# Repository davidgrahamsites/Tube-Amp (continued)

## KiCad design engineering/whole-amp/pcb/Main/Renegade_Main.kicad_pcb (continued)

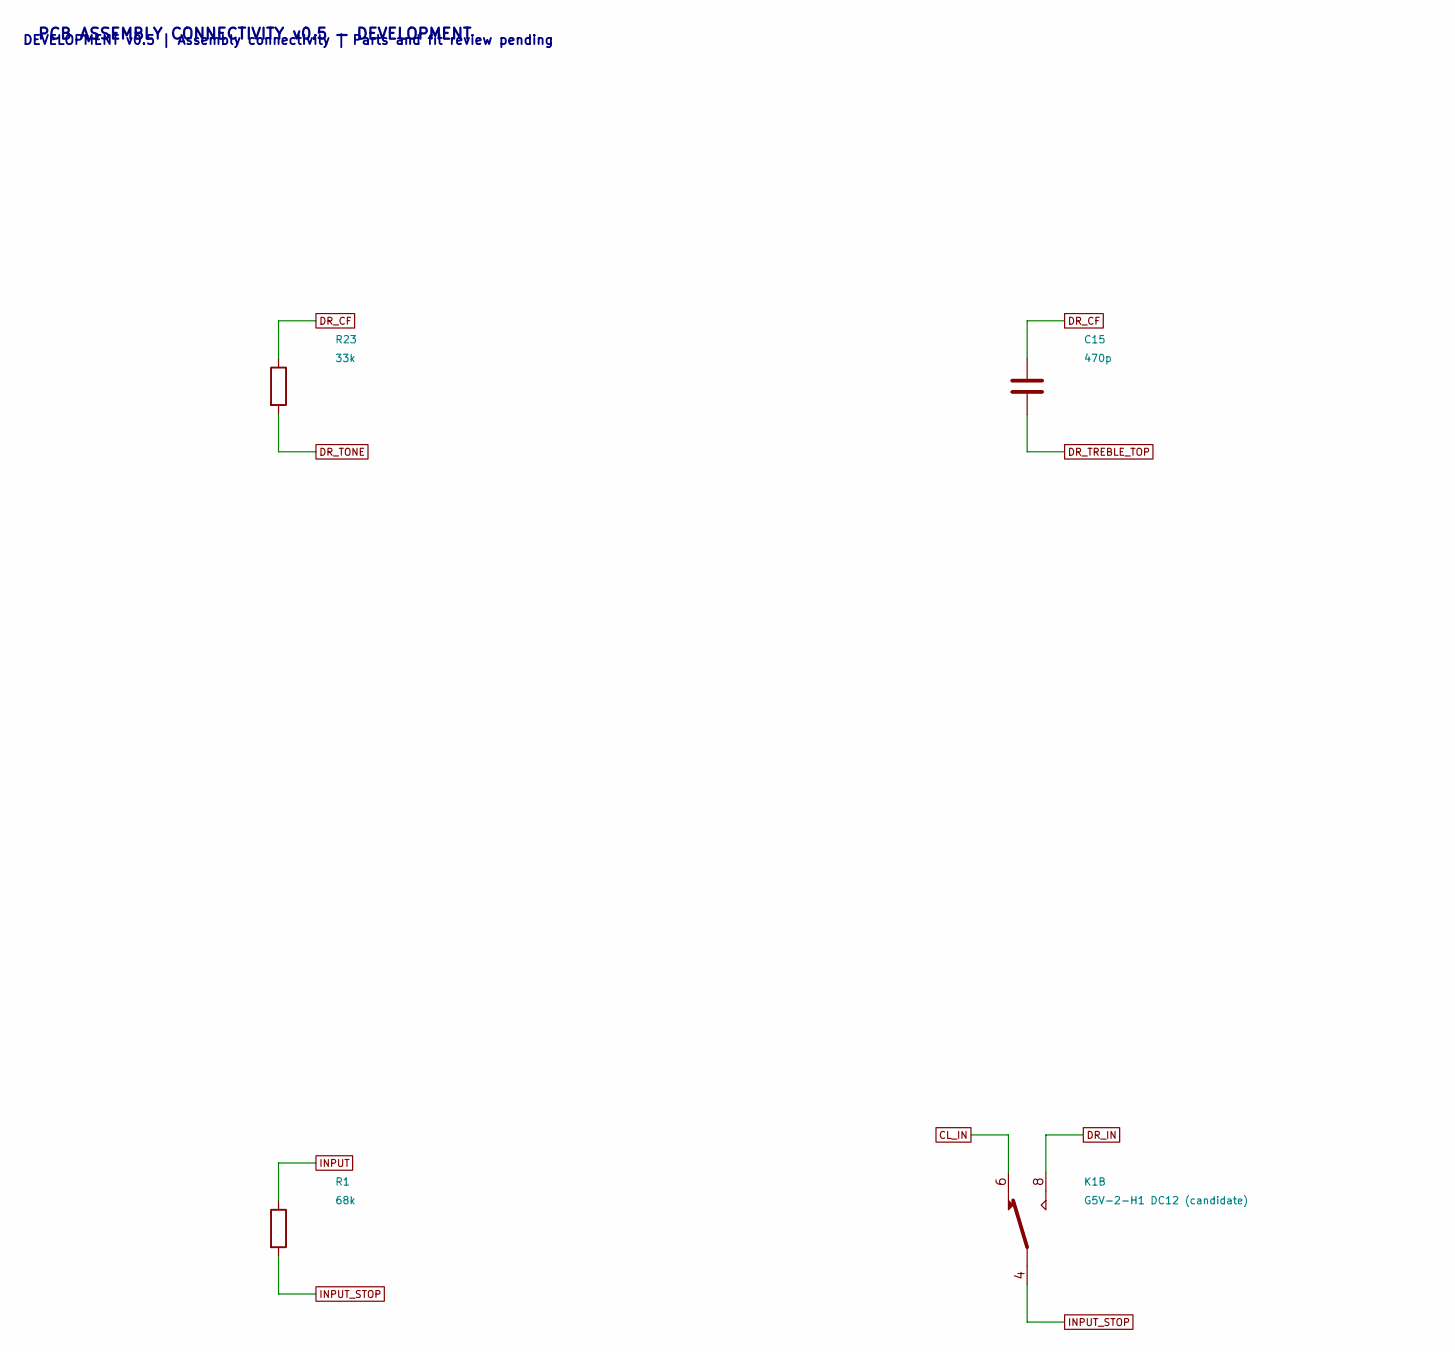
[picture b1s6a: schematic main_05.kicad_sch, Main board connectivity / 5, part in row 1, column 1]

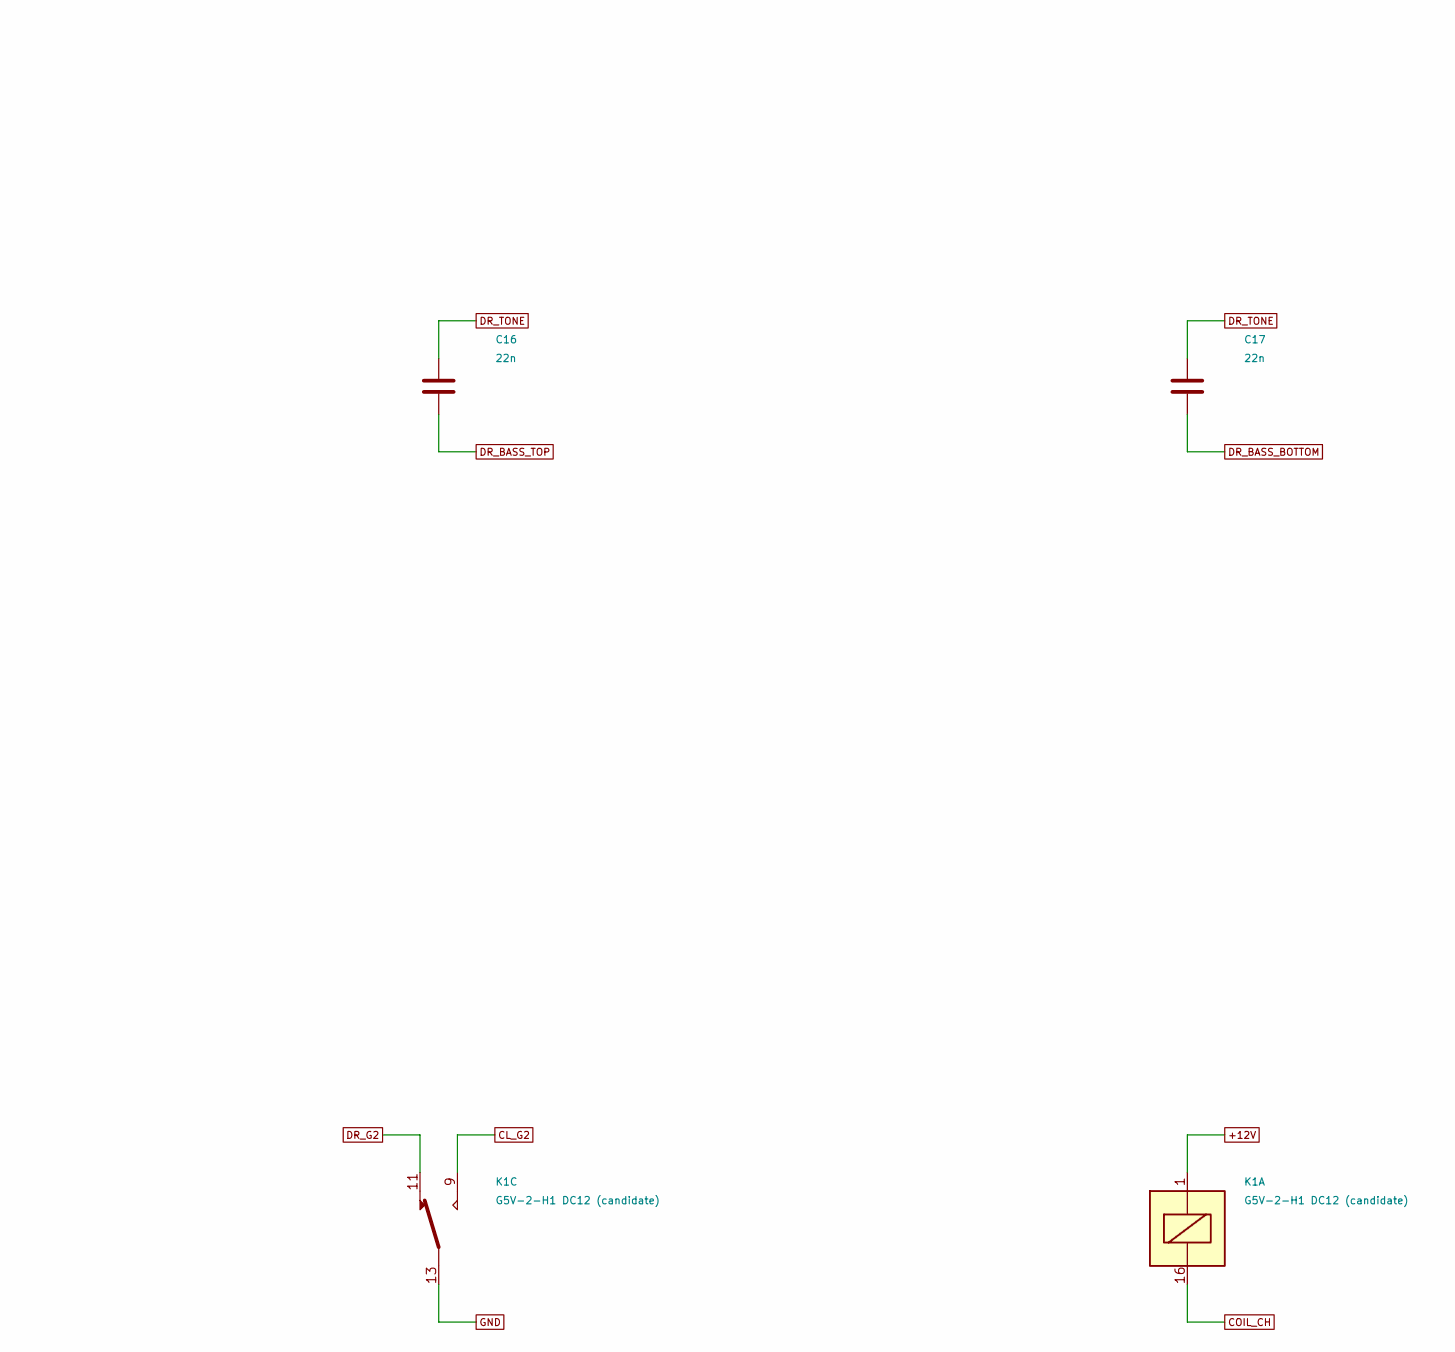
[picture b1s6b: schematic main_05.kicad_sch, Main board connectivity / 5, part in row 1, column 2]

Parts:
C15: 470p; C_Disc_D7.5mm_W5.0mm_P10.00mm; Rating 630 V film
C16, C17: 22n; C_Rect_L18.0mm_W7.0mm_P15.00mm_FKS3_FKP3; Rating 630 V film
K1: G5V-2-H1 DC12 (candidate); Relay_DPDT_Omron_G5V-2; Rating 12 V high-sensitivity coil; 150 mW refe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
R1: 68k; R_Axial_DIN0207_L6.3mm_D2.5mm_P15.24mm_Horizontal; Rating 0.5 W minimum; exact part pending
R23: 33k; R_Axial_DIN0207_L6.3mm_D2.5mm_P15.24mm_Horizontal; Rating 0.5 W minimum; exact part pending

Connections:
+12V: K1.1; also elsewhere on the board
CL_G2: K1.9; also elsewhere on the board
CL_IN: K1.6; also elsewhere on the board
COIL_CH: K1.16; also elsewhere on the board
DR_BASS_BOTTOM: C17.2; also elsewhere on the board
DR_BASS_TOP: C16.2; also elsewhere on the board
DR_CF: C15.1, R23.1; also elsewhere on the board
DR_G2: K1.11; also elsewhere on the board
DR_IN: K1.8; also elsewhere on the board
DR_TONE: C16.1, C17.1, R23.2
DR_TREBLE_TOP: C15.2; also elsewhere on the board
GND: K1.13; also elsewhere on the board
INPUT: R1.1; also elsewhere on the board
INPUT_STOP: K1.4, R1.2

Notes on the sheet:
PCB ASSEMBLY CONNECTIVITY v0.5 — DEVELOPMENT
DEVELOPMENT v0.5 | Assembly connectivity | Parts and fit review pending

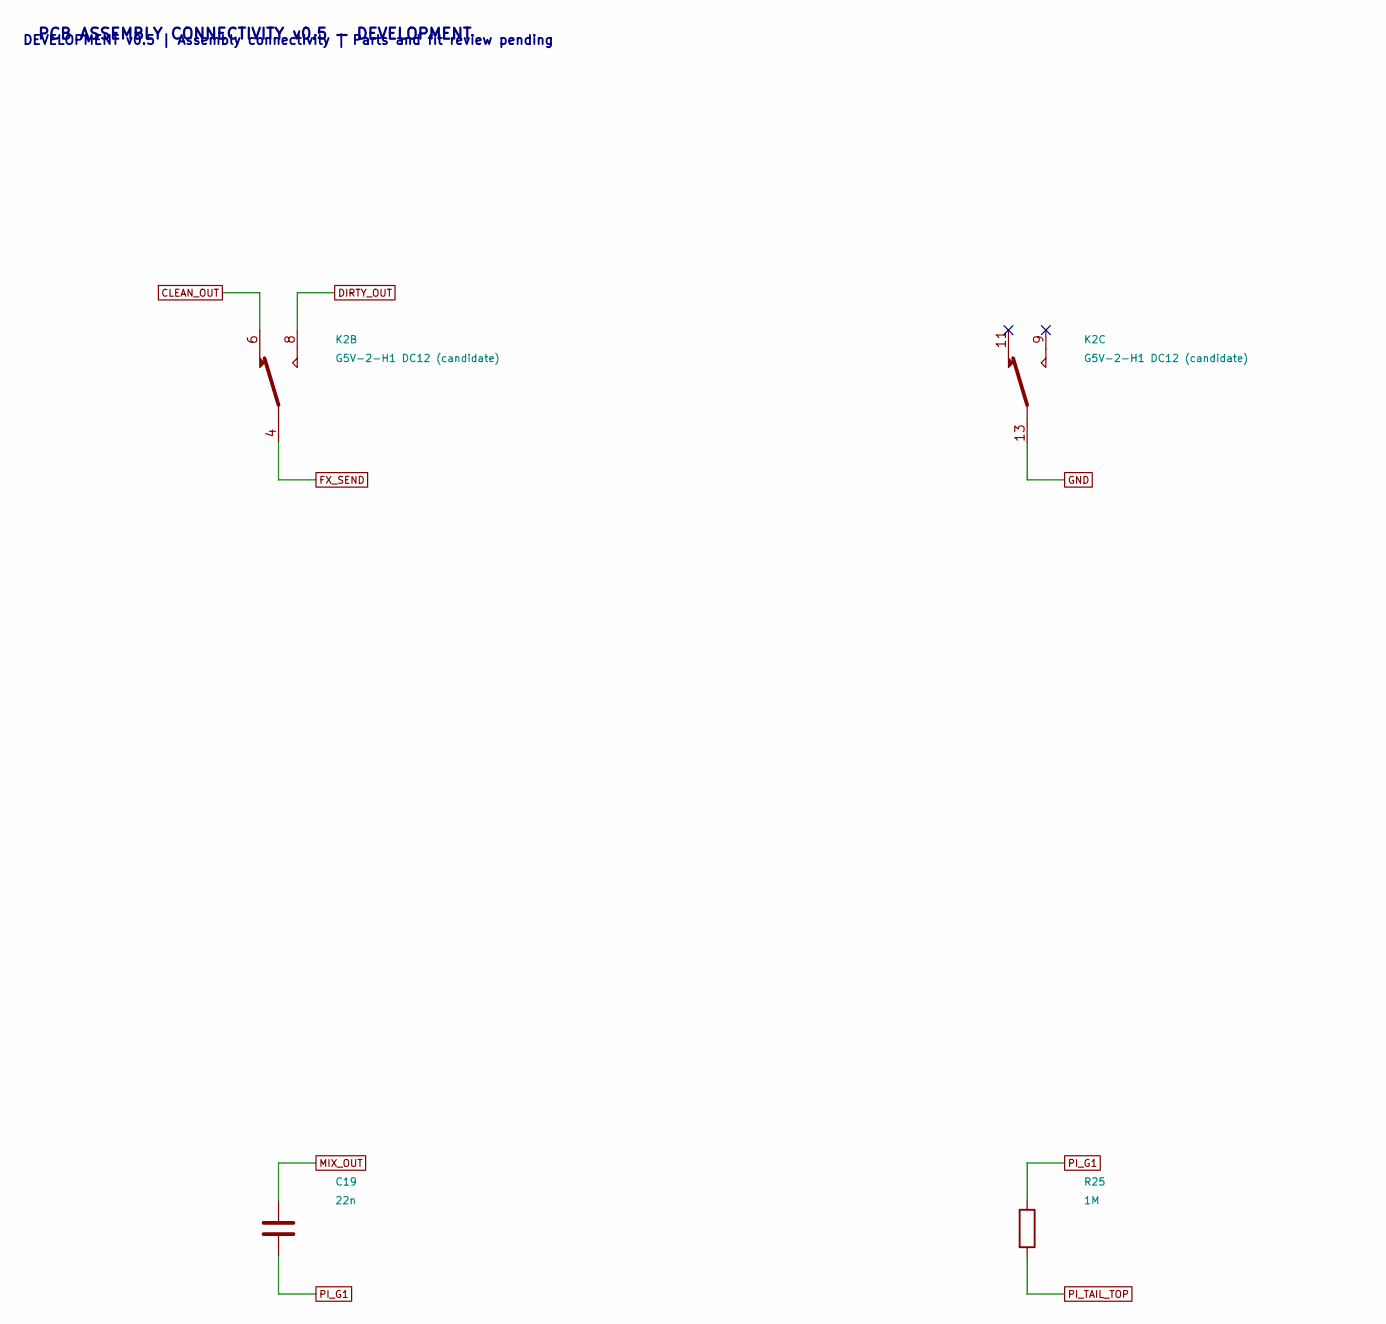
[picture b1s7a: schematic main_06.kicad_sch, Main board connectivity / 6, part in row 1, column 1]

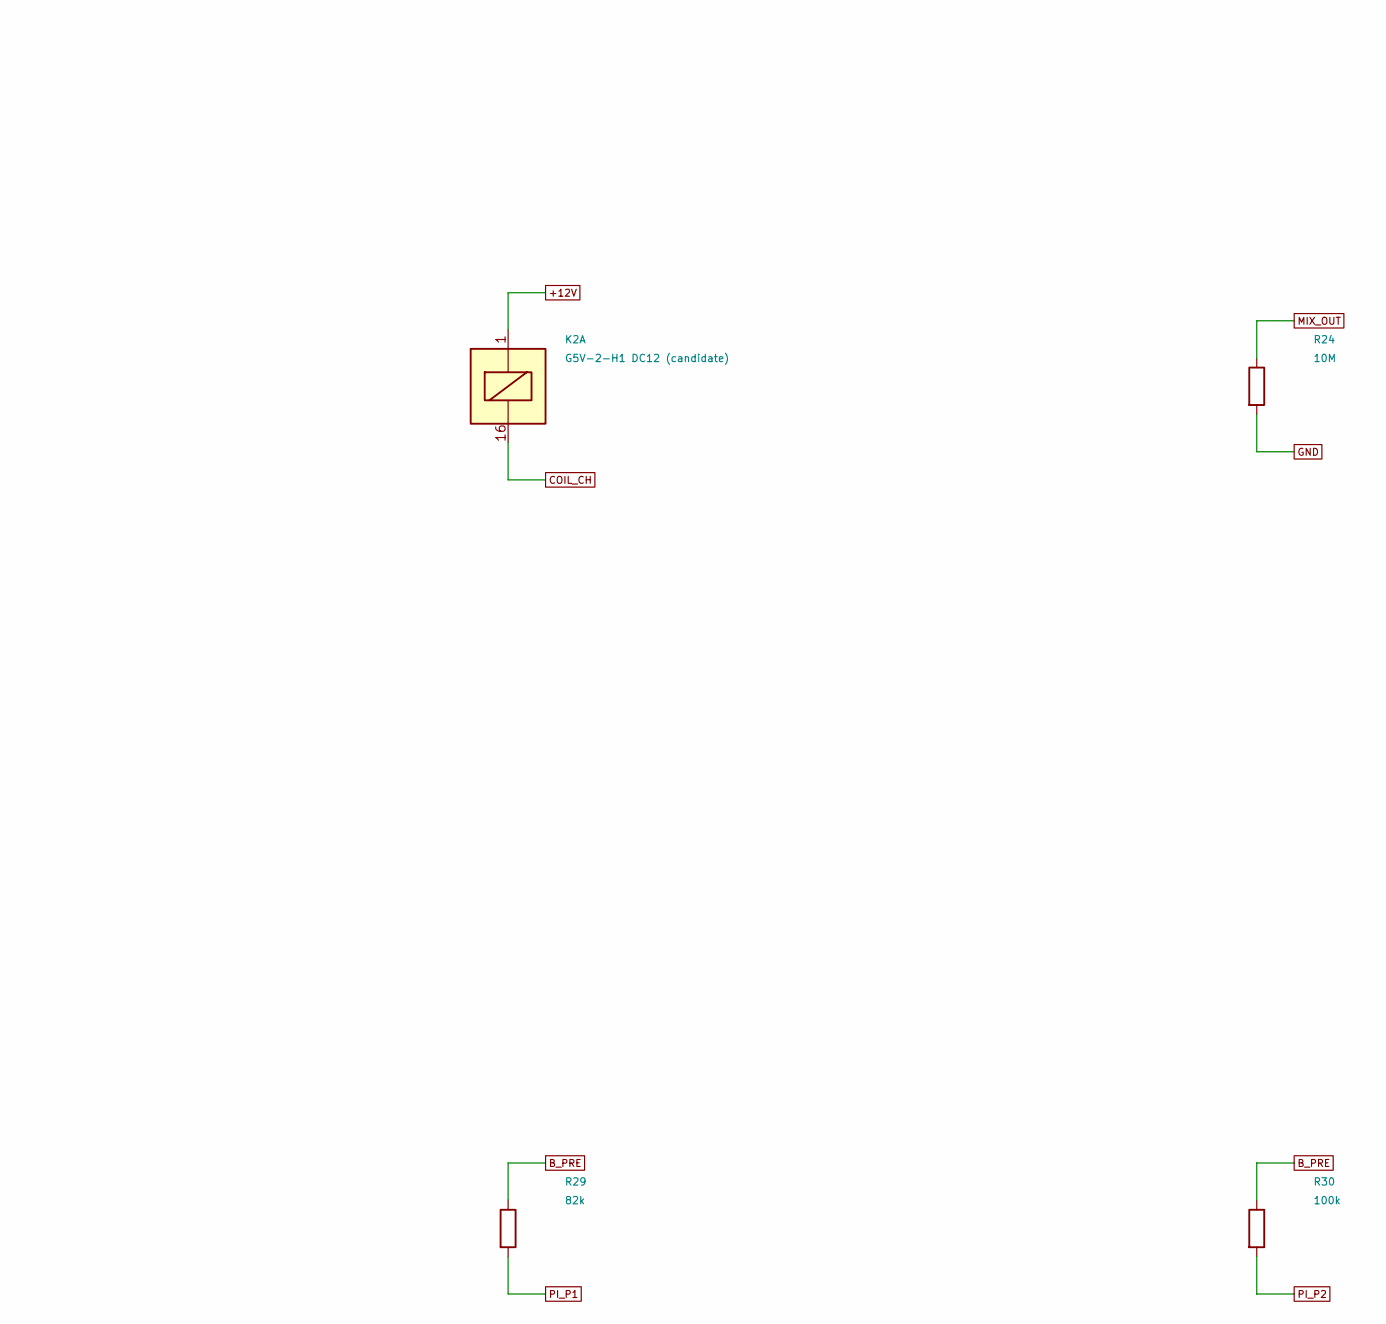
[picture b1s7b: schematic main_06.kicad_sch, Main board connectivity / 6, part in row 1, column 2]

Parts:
C19: 22n; C_Rect_L18.0mm_W7.0mm_P15.00mm_FKS3_FKP3; Rating 630 V film
K2: G5V-2-H1 DC12 (candidate); Relay_DPDT_Omron_G5V-2; Rating 12 V high-sensitivity coil; 150 mW refe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
R24: 10M; R_Axial_DIN0207_L6.3mm_D2.5mm_P15.24mm_Horizontal; Rating 0.5 W minimum; exact part pending
R25: 1M; R_Axial_DIN0207_L6.3mm_D2.5mm_P15.24mm_Horizontal; Rating 0.5 W minimum; exact part pending
R29: 82k; R_Axial_DIN0207_L6.3mm_D2.5mm_P15.24mm_Horizontal; Rating 0.5 W minimum; exact part pending
R30: 100k; R_Axial_DIN0207_L6.3mm_D2.5mm_P15.24mm_Horizontal; Rating 0.5 W minimum; exact part pending

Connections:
+12V: K2.1; also elsewhere on the board
B_PRE: R29.1, R30.1; also elsewhere on the board
CLEAN_OUT: K2.6; also elsewhere on the board
COIL_CH: K2.16; also elsewhere on the board
DIRTY_OUT: K2.8; also elsewhere on the board
FX_SEND: K2.4; also elsewhere on the board
GND: K2.13, R24.2; also elsewhere on the board
MIX_OUT: C19.1, R24.1; also elsewhere on the board
PI_G1: C19.2, R25.1; also elsewhere on the board
PI_P1: R29.2; also elsewhere on the board
PI_P2: R30.2; also elsewhere on the board
PI_TAIL_TOP: R25.2; also elsewhere on the board

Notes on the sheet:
PCB ASSEMBLY CONNECTIVITY v0.5 — DEVELOPMENT
DEVELOPMENT v0.5 | Assembly connectivity | Parts and fit review pending

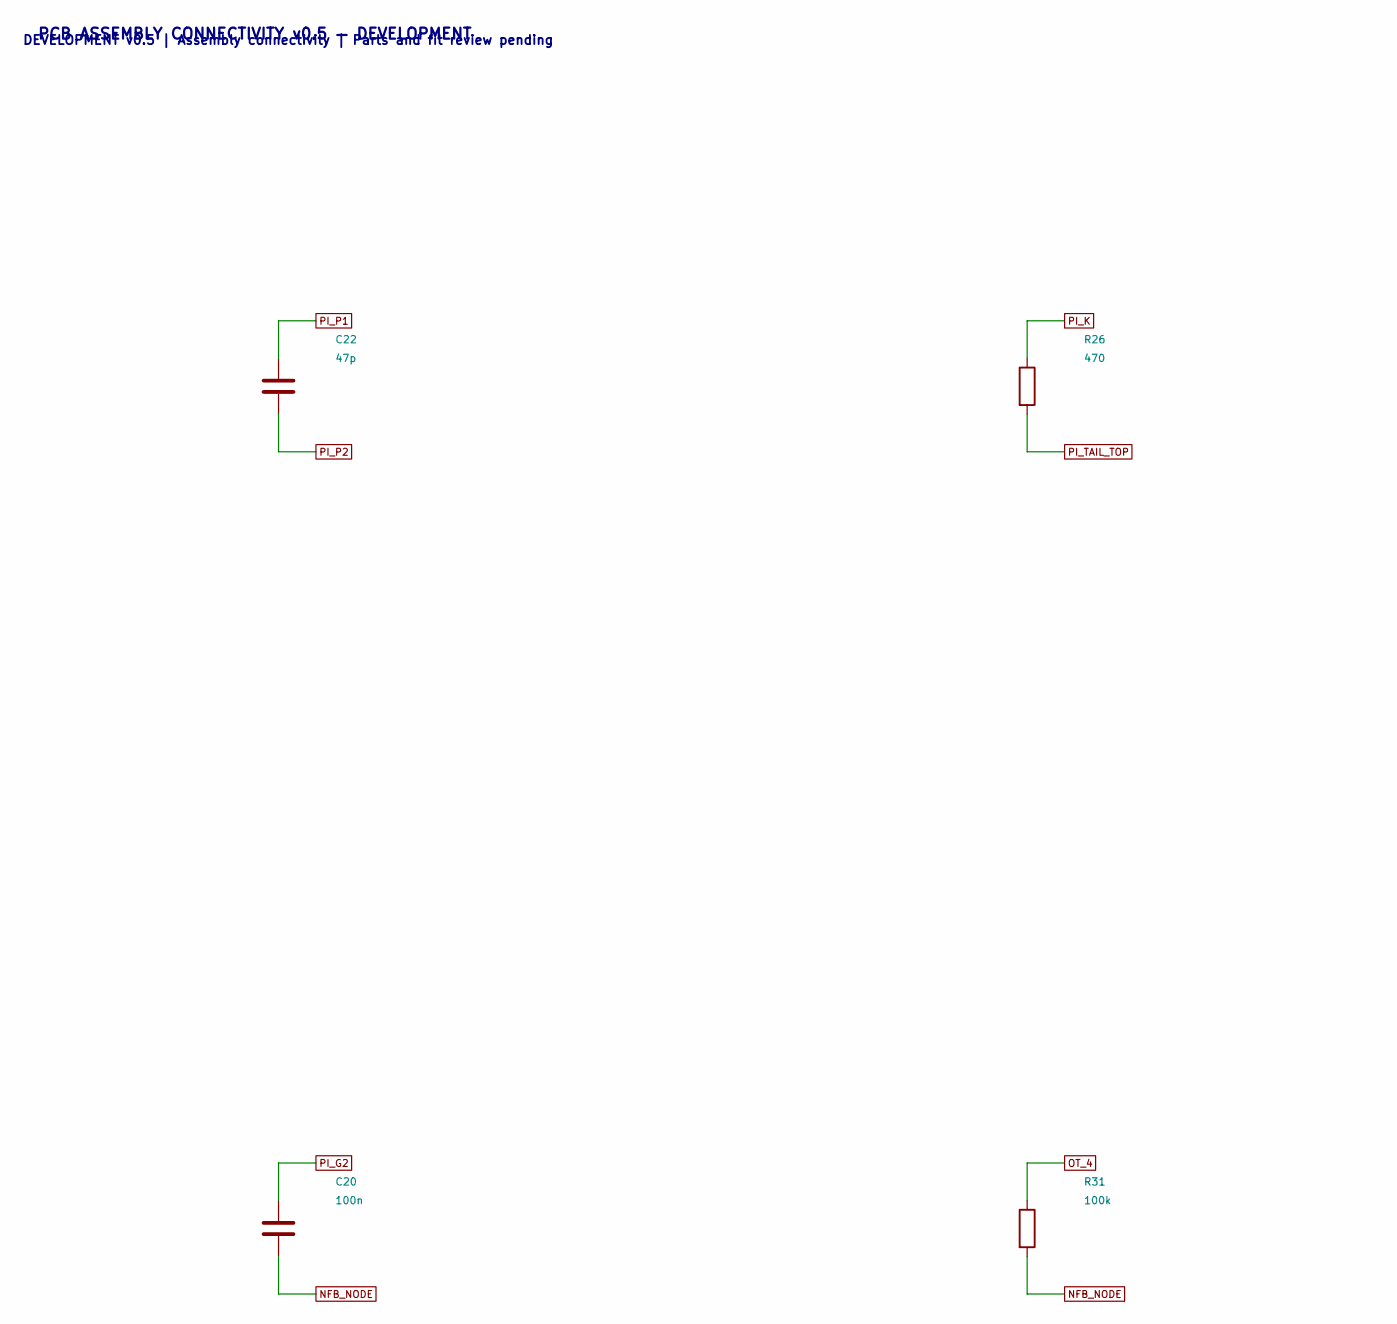
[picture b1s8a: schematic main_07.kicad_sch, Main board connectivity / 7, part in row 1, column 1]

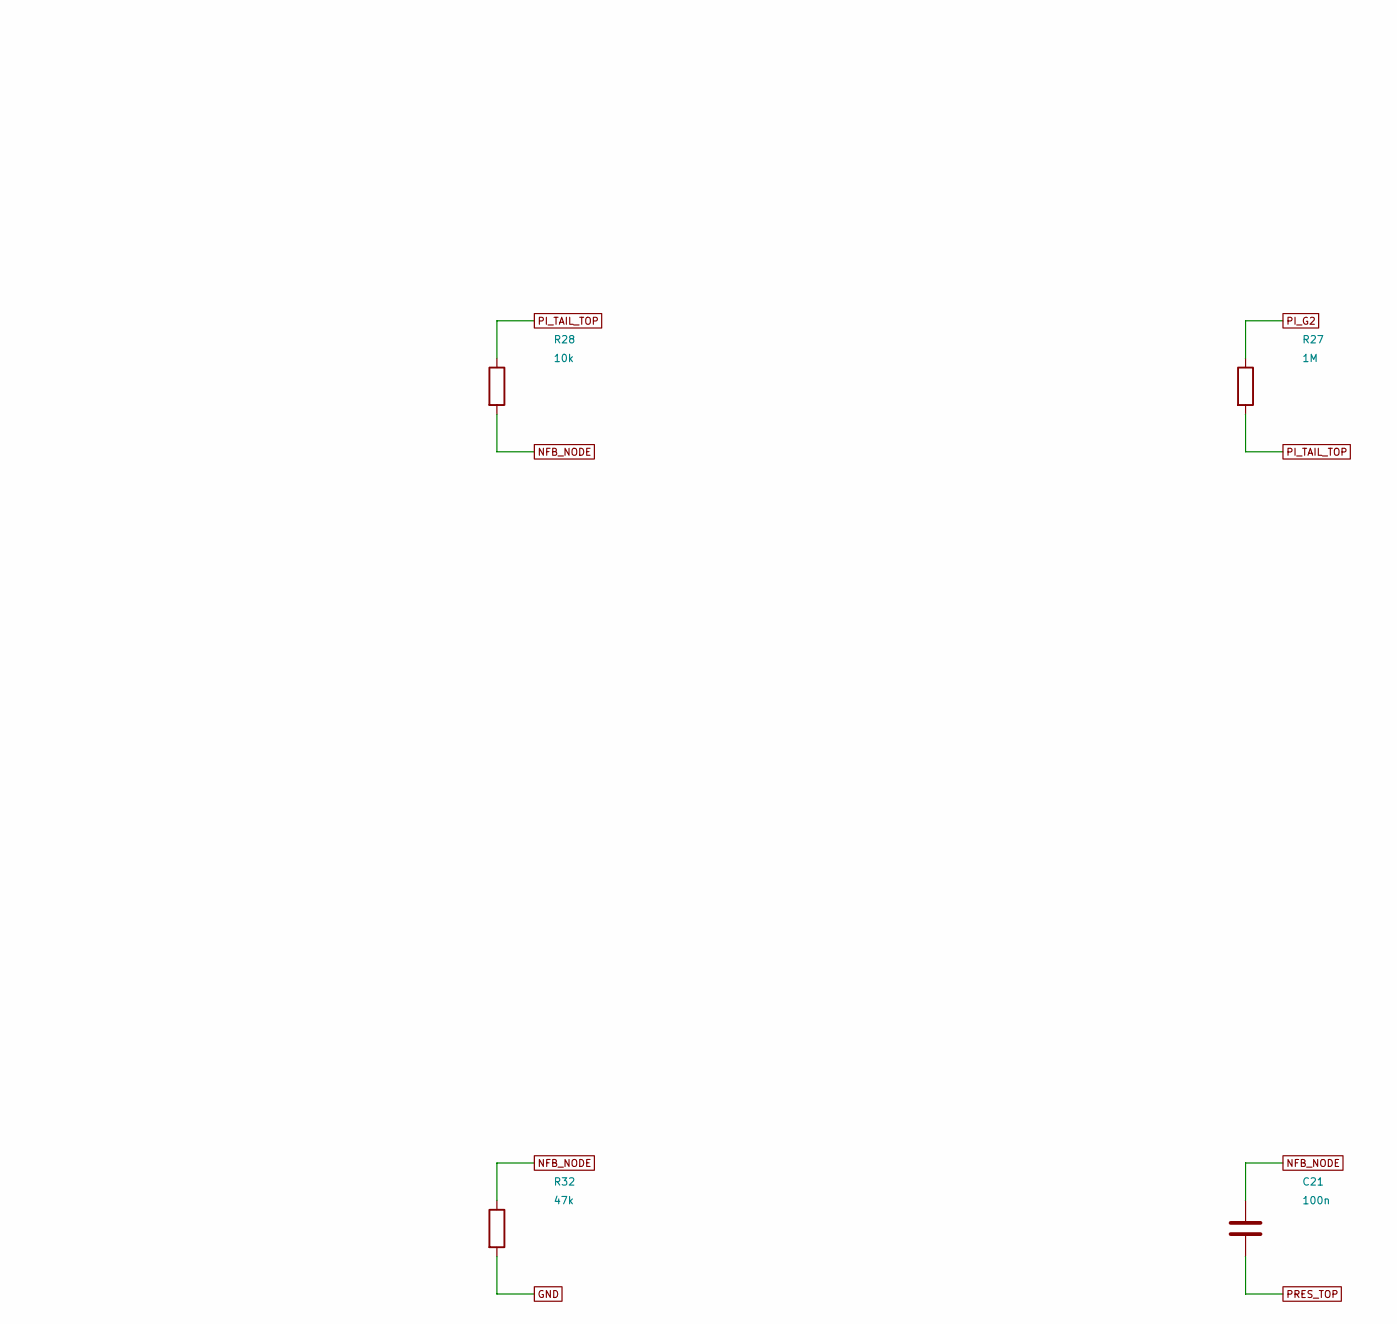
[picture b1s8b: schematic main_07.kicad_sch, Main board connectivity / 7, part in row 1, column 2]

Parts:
C20, C21: 100n; C_Rect_L18.0mm_W7.0mm_P15.00mm_FKS3_FKP3; Rating 630 V film
C22: 47p; C_Disc_D7.5mm_W5.0mm_P10.00mm; Rating 630 V film
R26: 470; R_Axial_DIN0207_L6.3mm_D2.5mm_P15.24mm_Horizontal; Rating 0.5 W minimum; exact part pending
R27: 1M; R_Axial_DIN0207_L6.3mm_D2.5mm_P15.24mm_Horizontal; Rating 0.5 W minimum; exact part pending
R28: 10k; R_Axial_DIN0207_L6.3mm_D2.5mm_P15.24mm_Horizontal; Rating 0.5 W minimum; exact part pending
R31: 100k; R_Axial_DIN0207_L6.3mm_D2.5mm_P15.24mm_Horizontal; Rating 0.5 W minimum; exact part pending
R32: 47k; R_Axial_DIN0207_L6.3mm_D2.5mm_P15.24mm_Horizontal; Rating 0.5 W minimum; exact part pending

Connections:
GND: R32.2; also elsewhere on the board
NFB_NODE: C20.2, C21.1, R28.2, R31.2, R32.1
OT_4: R31.1; also elsewhere on the board
PI_G2: C20.1, R27.1; also elsewhere on the board
PI_K: R26.1; also elsewhere on the board
PI_P1: C22.1; also elsewhere on the board
PI_P2: C22.2; also elsewhere on the board
PI_TAIL_TOP: R26.2, R27.2, R28.1; also elsewhere on the board
PRES_TOP: C21.2; also elsewhere on the board

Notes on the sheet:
PCB ASSEMBLY CONNECTIVITY v0.5 — DEVELOPMENT
DEVELOPMENT v0.5 | Assembly connectivity | Parts and fit review pending

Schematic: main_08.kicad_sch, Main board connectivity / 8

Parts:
C23, C24: 22n; C_Rect_L18.0mm_W7.0mm_P15.00mm_FKS3_FKP3; Rating 630 V film
JM001: +12V; WirePad_1.3mm; Rating Soldered and strain-relieved wire, volt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
JM002: BIAS_OUT; WirePad_1.3mm; Rating Soldered and strain-relieved wire, volt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
JM003: B_EARLY; WirePad_1.3mm; Rating Soldered and strain-relieved wire, volt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
JM004: B_PRE; WirePad_1.3mm; Rating Soldered and strain-relieved wire, volt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
R33, R34: 220k; R_Axial_DIN0207_L6.3mm_D2.5mm_P15.24mm_Horizontal; Rating 0.5 W minimum; exact part pending

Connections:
+12V: JM001.1; also elsewhere on the board
BIAS_OUT: JM002.1, R33.2, R34.2
B_EARLY: JM003.1; also elsewhere on the board
B_PRE: JM004.1; also elsewhere on the board
GRID_A_FEED: C23.2, R33.1; also elsewhere on the board
GRID_B_FEED: C24.2, R34.1; also elsewhere on the board
PI_P1: C23.1; also elsewhere on the board
PI_P2: C24.1; also elsewhere on the board

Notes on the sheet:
PCB ASSEMBLY CONNECTIVITY v0.5 — DEVELOPMENT
DEVELOPMENT v0.5 | Assembly connectivity | Parts and fit review pending

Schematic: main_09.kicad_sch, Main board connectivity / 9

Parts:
JM005: CL_BASS_BOTTOM; WirePad_1.3mm; Rating Soldered and strain-relieved wire, volt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
JM006: CL_BASS_TOP; WirePad_1.3mm; Rating Soldered and strain-relieved wire, volt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
JM007: CL_G2; WirePad_1.3mm; Rating Soldered and strain-relieved wire, volt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
JM008: CL_IN; WirePad_1.3mm; Rating Soldered and strain-relieved wire, volt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
JM009: CL_K1; WirePad_1.3mm; Rating Soldered and strain-relieved wire, volt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
JM010: CL_K2; WirePad_1.3mm; Rating Soldered and strain-relieved wire, volt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
JM011: CL_P1; WirePad_1.3mm; Rating Soldered and strain-relieved wire, volt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
JM012: CL_P2; WirePad_1.3mm; Rating Soldered and strain-relieved wire, volt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

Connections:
CL_BASS_BOTTOM: JM005.1; also elsewhere on the board
CL_BASS_TOP: JM006.1; also elsewhere on the board
CL_G2: JM007.1; also elsewhere on the board
CL_IN: JM008.1; also elsewhere on the board
CL_K1: JM009.1; also elsewhere on the board
CL_K2: JM010.1; also elsewhere on the board
CL_P1: JM011.1; also elsewhere on the board
CL_P2: JM012.1; also elsewhere on the board

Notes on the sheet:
PCB ASSEMBLY CONNECTIVITY v0.5 — DEVELOPMENT
DEVELOPMENT v0.5 | Assembly connectivity | Parts and fit review pending

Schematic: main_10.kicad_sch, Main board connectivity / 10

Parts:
JM013: CL_TREBLE_TOP; WirePad_1.3mm; Rating Soldered and strain-relieved wire, volt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
JM014: COIL_CH; WirePad_1.3mm; Rating Soldered and strain-relieved wire, volt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
JM015: DIRTY_OUT; WirePad_1.3mm; Rating Soldered and strain-relieved wire, volt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
JM016: DR_BASS_BOTTOM; WirePad_1.3mm; Rating Soldered and strain-relieved wire, volt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
JM017: DR_BASS_TOP; WirePad_1.3mm; Rating Soldered and strain-relieved wire, volt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
JM018: DR_CF; WirePad_1.3mm; Rating Soldered and strain-relieved wire, volt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
JM019: DR_G2; WirePad_1.3mm; Rating Soldered and strain-relieved wire, volt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
JM020: DR_G3; WirePad_1.3mm; Rating Soldered and strain-relieved wire, volt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

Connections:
CL_TREBLE_TOP: JM013.1; also elsewhere on the board
COIL_CH: JM014.1; also elsewhere on the board
DIRTY_OUT: JM015.1; also elsewhere on the board
DR_BASS_BOTTOM: JM016.1; also elsewhere on the board
DR_BASS_TOP: JM017.1; also elsewhere on the board
DR_CF: JM018.1; also elsewhere on the board
DR_G2: JM019.1; also elsewhere on the board
DR_G3: JM020.1; also elsewhere on the board

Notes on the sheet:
PCB ASSEMBLY CONNECTIVITY v0.5 — DEVELOPMENT
DEVELOPMENT v0.5 | Assembly connectivity | Parts and fit review pending

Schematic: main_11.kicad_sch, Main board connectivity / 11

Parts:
JM021: DR_GAIN_TOP; WirePad_1.3mm; Rating Soldered and strain-relieved wire, volt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
JM022: DR_GAIN_W; WirePad_1.3mm; Rating Soldered and strain-relieved wire, volt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
JM023: DR_IN; WirePad_1.3mm; Rating Soldered and strain-relieved wire, volt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
JM024: DR_K1; WirePad_1.3mm; Rating Soldered and strain-relieved wire, volt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
JM025: DR_K2; WirePad_1.3mm; Rating Soldered and strain-relieved wire, volt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
JM026: DR_K3; WirePad_1.3mm; Rating Soldered and strain-relieved wire, volt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
JM027: DR_P1; WirePad_1.3mm; Rating Soldered and strain-relieved wire, volt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
JM028: DR_P2; WirePad_1.3mm; Rating Soldered and strain-relieved wire, volt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

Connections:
DR_GAIN_TOP: JM021.1; also elsewhere on the board
DR_GAIN_W: JM022.1; also elsewhere on the board
DR_IN: JM023.1; also elsewhere on the board
DR_K1: JM024.1; also elsewhere on the board
DR_K2: JM025.1; also elsewhere on the board
DR_K3: JM026.1; also elsewhere on the board
DR_P1: JM027.1; also elsewhere on the board
DR_P2: JM028.1; also elsewhere on the board

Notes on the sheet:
PCB ASSEMBLY CONNECTIVITY v0.5 — DEVELOPMENT
DEVELOPMENT v0.5 | Assembly connectivity | Parts and fit review pending

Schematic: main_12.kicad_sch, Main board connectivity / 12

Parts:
JM029: DR_P3; WirePad_1.3mm; Rating Soldered and strain-relieved wire, volt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
JM030: DR_TREBLE_TOP; WirePad_1.3mm; Rating Soldered and strain-relieved wire, volt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
JM031: FX_SEND; WirePad_1.3mm; Rating Soldered and strain-relieved wire, volt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
JM032: GND; WirePad_1.3mm; Rating Soldered and strain-relieved wire, volt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
JM033: GRID_A_FEED; WirePad_1.3mm; Rating Soldered and strain-relieved wire, volt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
JM034: GRID_B_FEED; WirePad_1.3mm; Rating Soldered and strain-relieved wire, volt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
JM035: INPUT; WirePad_1.3mm; Rating Soldered and strain-relieved wire, volt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
JM036: MIX_OUT; WirePad_1.3mm; Rating Soldered and strain-relieved wire, volt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

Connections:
DR_P3: JM029.1; also elsewhere on the board
DR_TREBLE_TOP: JM030.1; also elsewhere on the board
FX_SEND: JM031.1; also elsewhere on the board
GND: JM032.1; also elsewhere on the board
GRID_A_FEED: JM033.1; also elsewhere on the board
GRID_B_FEED: JM034.1; also elsewhere on the board
INPUT: JM035.1; also elsewhere on the board
MIX_OUT: JM036.1; also elsewhere on the board

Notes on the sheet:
PCB ASSEMBLY CONNECTIVITY v0.5 — DEVELOPMENT
DEVELOPMENT v0.5 | Assembly connectivity | Parts and fit review pending

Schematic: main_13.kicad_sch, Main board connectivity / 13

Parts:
H1: MountingHole_3.2mm_M3
JM037: OT_4; WirePad_1.3mm; Rating Soldered and strain-relieved wire, volt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
JM038: PI_G1; WirePad_1.3mm; Rating Soldered and strain-relieved wire, volt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
JM039: PI_G2; WirePad_1.3mm; Rating Soldered and strain-relieved wire, volt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
JM040: PI_K; WirePad_1.3mm; Rating Soldered and strain-relieved wire, volt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
JM041: PI_P1; WirePad_1.3mm; Rating Soldered and strain-relieved wire, volt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
JM042: PI_P2; WirePad_1.3mm; Rating Soldered and strain-relieved wire, volt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
JM043: PRES_TOP; WirePad_1.3mm; Rating Soldered and strain-relieved wire, volt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

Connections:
OT_4: JM037.1; also elsewhere on the board
PI_G1: JM038.1; also elsewhere on the board
PI_G2: JM039.1; also elsewhere on the board
PI_K: JM040.1; also elsewhere on the board
PI_P1: JM041.1; also elsewhere on the board
PI_P2: JM042.1; also elsewhere on the board
PRES_TOP: JM043.1; also elsewhere on the board

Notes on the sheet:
PCB ASSEMBLY CONNECTIVITY v0.5 — DEVELOPMENT
DEVELOPMENT v0.5 | Assembly connectivity | Parts and fit review pending

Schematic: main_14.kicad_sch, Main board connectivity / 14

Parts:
H2, H3, H4: MountingHole_3.2mm_M3

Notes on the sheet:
PCB ASSEMBLY CONNECTIVITY v0.5 — DEVELOPMENT
DEVELOPMENT v0.5 | Assembly connectivity | Parts and fit review pending

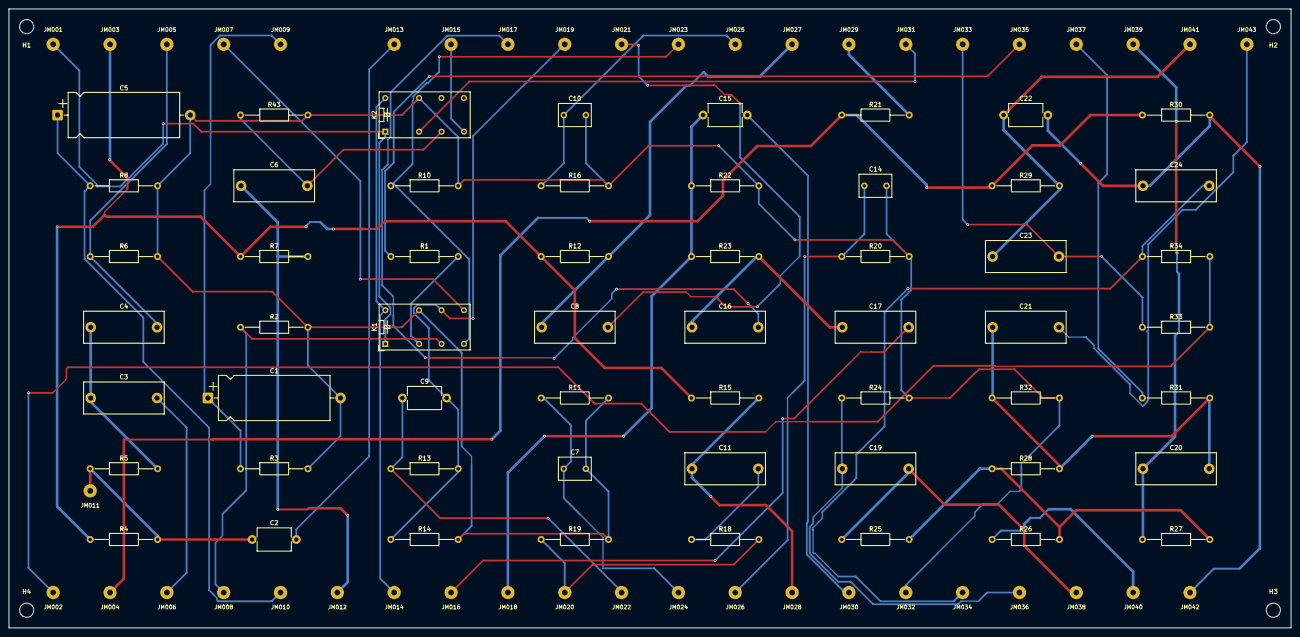
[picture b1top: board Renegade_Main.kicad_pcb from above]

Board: 2 copper layers, 290.0 x 140.0 mm, 103 parts (0 on the bottom side), 50 nets.

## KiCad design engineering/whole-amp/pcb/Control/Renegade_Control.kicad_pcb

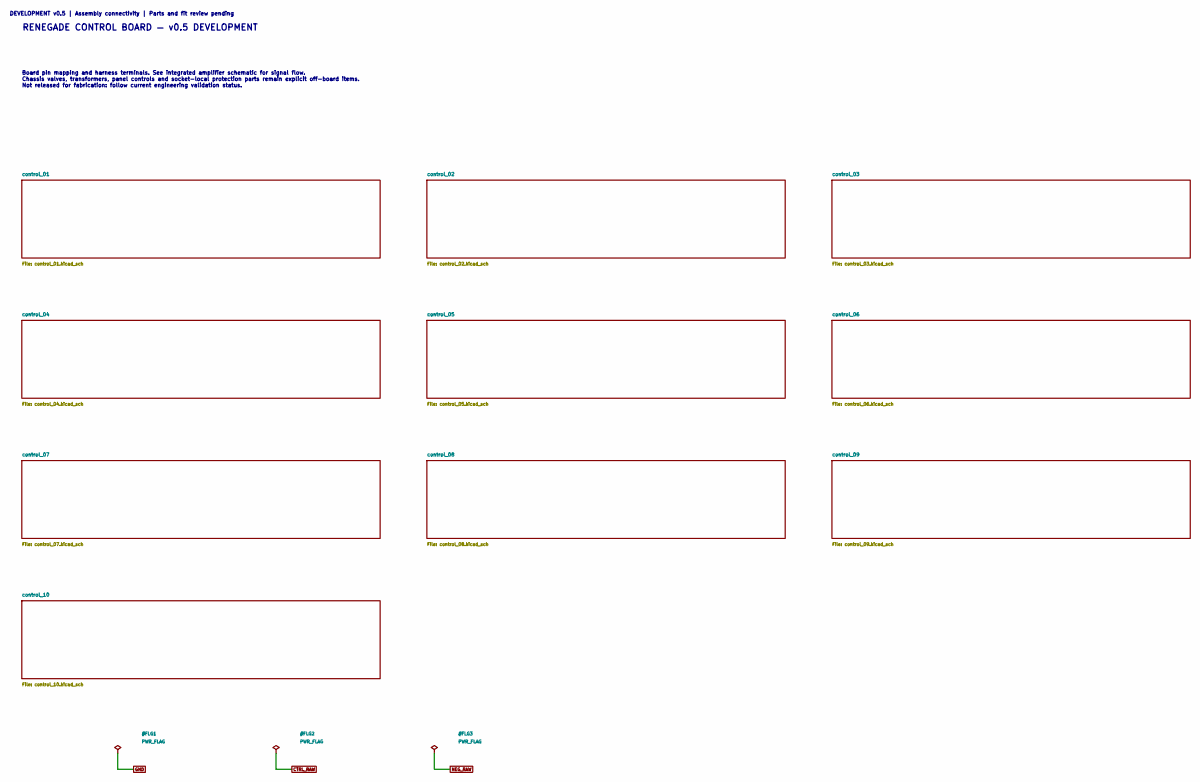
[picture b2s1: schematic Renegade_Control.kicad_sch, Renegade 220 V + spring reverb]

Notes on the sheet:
RENEGADE CONTROL BOARD — v0.5 DEVELOPMENT
Board pin mapping and harness terminals. See integrated amplifier schematic for signal flow. Chassis valves, transformers, panel controls and socket-local protection parts remain explicit off-board items. Not released for fabrication: follow current engineering validation status.
DEVELOPMENT v0.5 | Assembly connectivity | Parts and fit review pending
